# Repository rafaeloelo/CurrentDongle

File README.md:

# USB Power & Current Meter Dongle (v1.0)

A custom-designed, inline USB power, voltage, and current meter built from scratch—covering schematic capture, PCB layout in KiCad, hand-soldering assembly, and bare-metal C firmware development for the STM32G030 microcontroller.

---

## Key Features

* **High-Precision Sensing:** Uses the Texas Instruments **INA226** bi-directional current and power monitor with a 16-bit Delta-Sigma ADC over a **10 mOhm (0.01 Ohm)** shunt resistor.
* **Hardware Signal Filtering:** Configured for hardware-level averaging of **64 samples** (register value 0x4727), effectively smoothing out high-frequency switching noise and pulsed current draws typical of modern USB SMPS chargers.
* **Hardware Power Calculation:** Internal calibration register (CAL = 5120) enables direct hardware multiplication for current (0.1 mA/LSB) and power (2.5 mW/LSB) readings without burdening the Cortex-M0+ core, which lacks a hardware FPU.
* **Non-Blocking Firmware Architecture:** Fully asynchronous main loop driven by HAL_GetTick() state timers with zero HAL_Delay() calls during normal operation.
* **Low-Power Optimization:** Utilizes the Cortex-M0+ Sleep Mode via the __WFI() (Wait For Interrupt) instruction at the end of every loop cycle, keeping the CPU core asleep for ~95% of the time between SysTick interrupts.
* **Live Diagnostics:** Dual status LEDs indicating real-time I2C bus health for both the OLED display (0x3C) and the INA226 sensor (0x40) (solid = OK, rapid 10 Hz blinking = device disconnected/NACK).
* **Crisp UI:** 128x64 **SSD1306 OLED** display refreshed at 5 Hz (200 ms intervals) for optimal readability.

---

## Hardware Architecture & Specifications

| Parameter | Specification |
| :--- | :--- |
| **Microcontroller** | STM32G030 (ARM Cortex-M0+) |
| **Current/Voltage Sensor** | TI INA226 (I2C Address: 0x40) |
| **Shunt Resistor** | 10 mOhm (0.01 Ohm) |
| **Display** | SSD1306 OLED 128x64 (I2C Address: 0x3C) |
| **Passive Footprint Size** | **0805** (selected specifically for manual soldering) |
| **Toolchain** | STM32CubeMX, CMake, Ninja, arm-none-eabi-gcc |

---

## Hardware Bring-Up, Assembly & Design Notes (Rev 1.0)

This board was designed with manual assembly and ease of debugging in mind:

1. **Hand-Soldering Friendly (0805 Passives):**  
   All passive components (resistors, capacitors, inductors) were intentionally chosen in the **0805 package**, allowing the entire PCB to be assembled cleanly using a standard **pencil soldering iron** without requiring a reflow oven or hot-air station.
2. **Power Tree & Unpopulated LDO Stage (U3, R12, C9, C10 - DNP):**  
   The initial schematic included an LDO linear voltage regulator stage (U3 along with R12, C9, and C10) downstream of the step-down buck converter. During step-by-step hardware bring-up, testing of the assembled switching converter revealed a stable output of **3.35 V**. Because this is well within the safe operating specifications for the STM32G030, INA226, and SSD1306, the LDO stage was left unpopulated (**DNP**) and bypassed.
3. **External Crystal Oscillator (HSE vs. HSI):**  
   Although the external crystal oscillator and its load capacitors were soldered onto the board, the HSE clock source was left inactive in the firmware. The MCU runs reliably on its internal **HSI RC oscillator (16 MHz)**, which provides more than enough timing accuracy for I2C communication and UI refresh intervals.
4. **Mechanical Notes for Rev 2.0 (OLED Mounting Holes):**  
   The four corner mounting holes originally placed for mechanical standoffs under the OLED module proved unnecessary. Soldering the display via its standard THT pin header provides rigid, more than sufficient mechanical stability. These mounting holes will be removed in Revision 2.0 to reduce the overall PCB footprint.

---

## Gallery

### KiCad Design & 3D Render

### Assembled Hardware

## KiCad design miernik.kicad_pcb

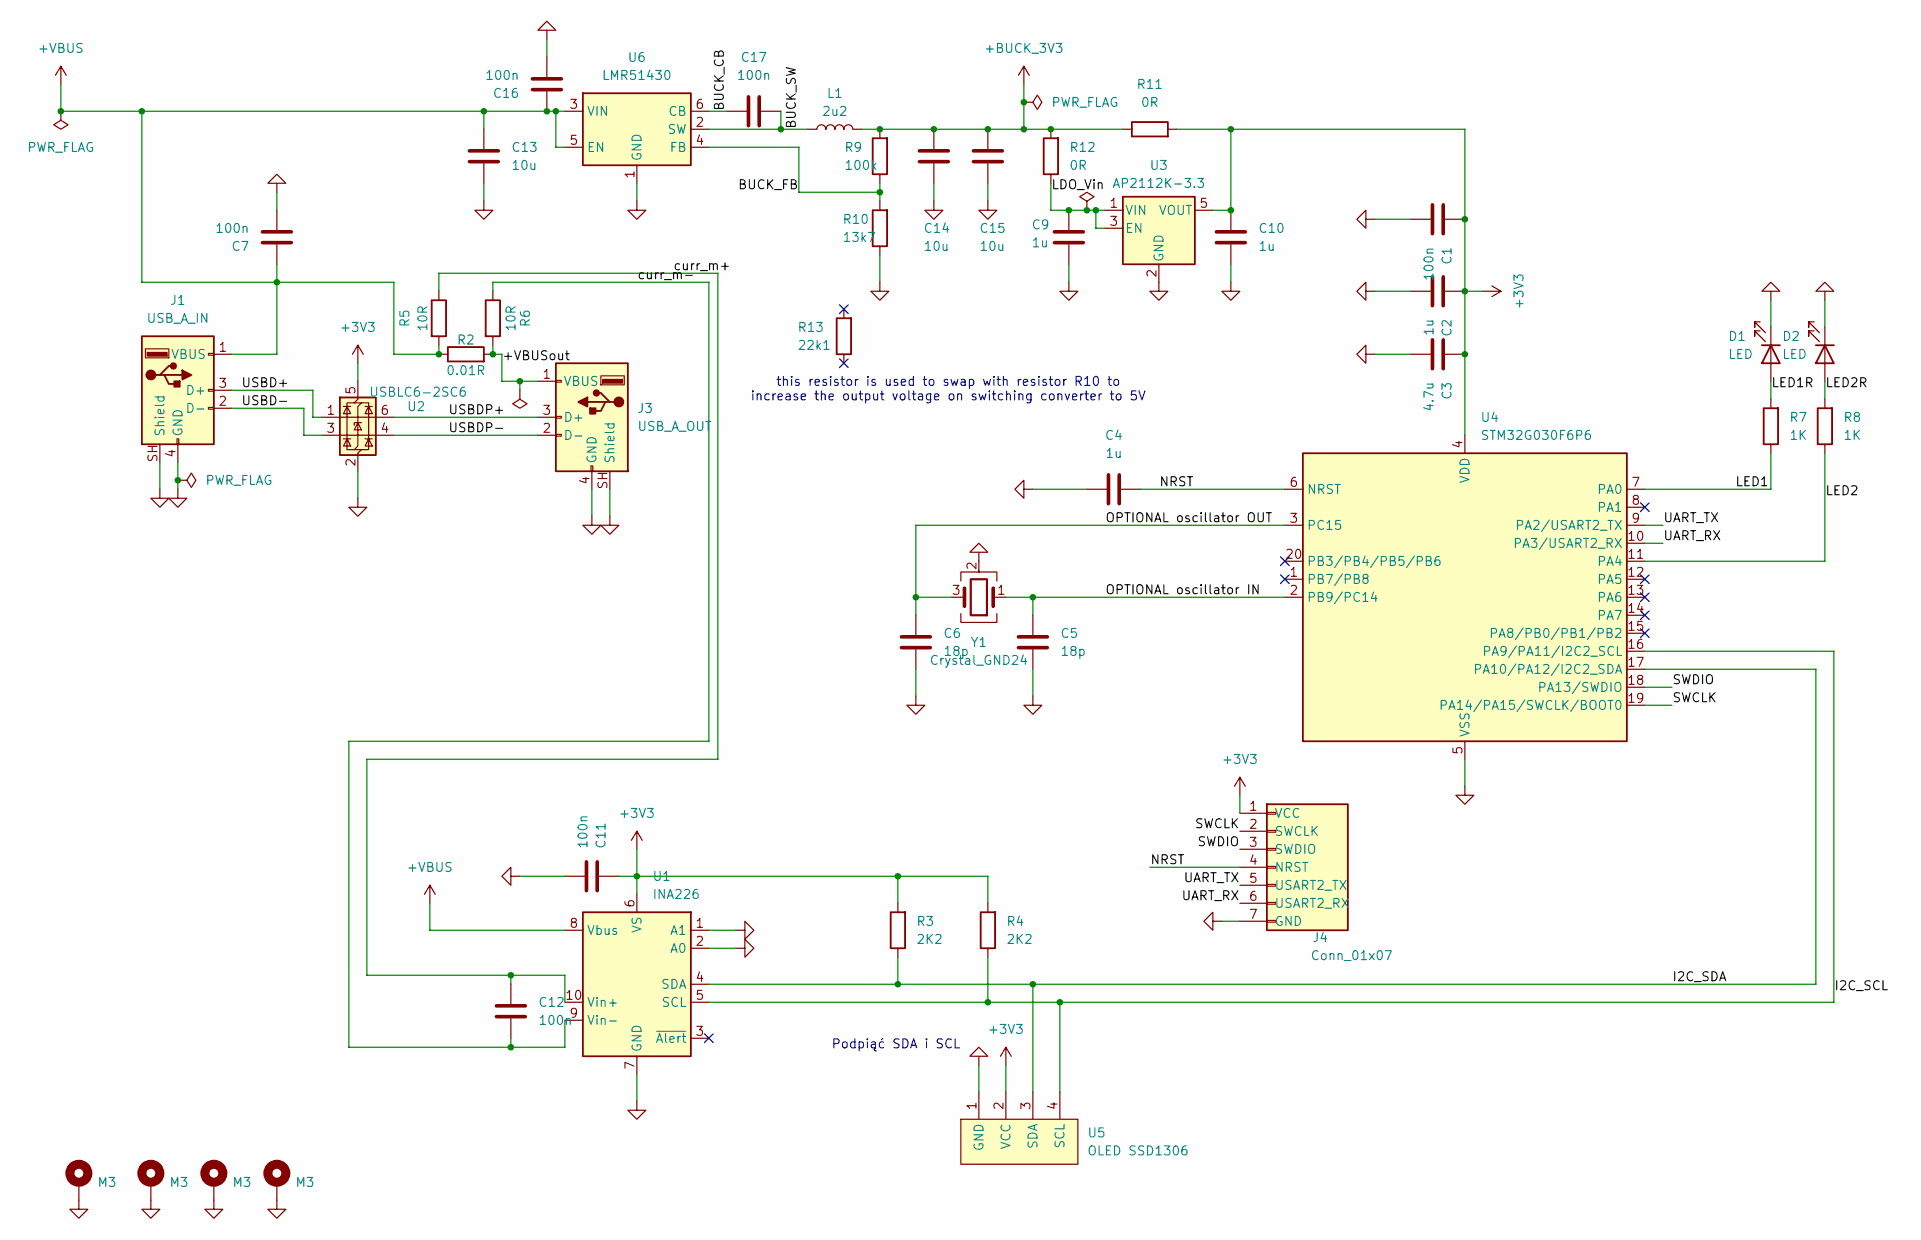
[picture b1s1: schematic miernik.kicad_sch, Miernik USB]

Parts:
C1, C7, C11, C12, C16, C17: 100n; C_0805_2012Metric
C2, C4, C9, C10: 1u; C_0805_2012Metric
C3: 4.7u; C_0805_2012Metric
C5, C6: 18p; C_0805_2012Metric
C13, C14, C15: 10u; C_0805_2012Metric
D1, D2: LED; LED_0805_2012Metric_Pad1.15x1.40mm_HandSolder
J1: USB_A_IN; USB_A_Molex_48037-2200_Horizontal
J3: USB_A_OUT; USB_A_Molex_67643_Horizontal
J4: Conn_01x07; PinSocket_1x07_P2.54mm_Vertical
L1: 2u2; L_0805_2012Metric_Pad1.05x1.20mm_HandSolder
MH1, MH2, MH3, MH4: M3; MountingHole_3.2mm_M3_Pad_Via
R2: 0.01R; R_2512_6332Metric_Pad1.40x3.35mm_HandSolder
R3, R4: 2K2; R_0805_2012Metric_Pad1.20x1.40mm_HandSolder
R5, R6: 10R; R_0805_2012Metric_Pad1.20x1.40mm_HandSolder
R7, R8: 1K; R_0805_2012Metric_Pad1.20x1.40mm_HandSolder
R9: 100k; R_0805_2012Metric_Pad1.20x1.40mm_HandSolder
R10: 13k7; R_0805_2012Metric_Pad1.20x1.40mm_HandSolder
R11, R12: 0R; R_0805_2012Metric_Pad1.20x1.40mm_HandSolder
R13: 22k1; R_0805_2012Metric_Pad1.20x1.40mm_HandSolder
U1: INA226; TSSOP-10_3x3mm_P0.5mm
U2: USBLC6-2SC6; SOT-23-6
U3: AP2112K-3.3; SOT-23-5
U4: STM32G030F6P6; TSSOP-20_4.4x6.5mm_P0.65mm
U5: OLED SSD1306; 128x64OLED
U6: LMR51430; SOT-23-6
Y1: Crystal_GND24; Crystal_SMD_3225-4Pin_3.2x2.5mm_HandSoldering

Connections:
+3V3: C1.1, C2.1, C3.1, C10.1, C11.1, J4.1 (VCC), R3.2, R4.2, R11.2, U1.6 (VS), U2.5 (VBUS), U3.5 (VOUT), U4.4 (VDD), U5.2 (VCC)
+BUCK_3V3: C14.1, C15.1, L1.2, R9.2, R11.1, R12.2
+VBUS: C7.1, C13.1, C16.1, J1.1 (VBUS), R2.1, R5.2, U1.8 (Vbus), U6.3 (VIN), U6.5 (EN)
/+VBUSout: J3.1 (VBUS), R2.2, R6.2
/BUCK_CB: C17.2, U6.6 (CB)
/BUCK_FB: R9.1, R10.2, U6.4 (FB)
/BUCK_SW: C17.1, L1.1, U6.2 (SW)
/I2C_SCL: R4.1, U1.5 (SCL), U4.16 (PA9/PA11/I2C2_SCL), U5.4 (SCL)
/I2C_SDA: R3.1, U1.4 (SDA), U4.17 (PA10/PA12/I2C2_SDA), U5.3 (SDA)
/LDO_Vin: C9.1, R12.1, U3.1 (VIN), U3.3 (EN)
/LED1: R7.1, U4.7 (PA0)
/LED1R: D1.2 (A), R7.2
/LED2: R8.1, U4.11 (PA4)
/LED2R: D2.2 (A), R8.2
/NRST: C4.1, J4.4 (NRST), U4.6 (NRST)
/OPTIONAL oscillator IN: C5.1, U4.2 (PB9/PC14), Y1.1
/OPTIONAL oscillator OUT: C6.1, U4.3 (PC15), Y1.3
/SWCLK: J4.2 (SWCLK), U4.19 (PA14/PA15/SWCLK/BOOT0)
/SWDIO: J4.3 (SWDIO), U4.18 (PA13/SWDIO)
/UART_RX: J4.6 (USART2_RX), U4.10 (PA3/USART2_RX)
/UART_TX: J4.5 (USART2_TX), U4.9 (PA2/USART2_TX)
/USBD+: J1.3 (D+), U2.1 (I/O1)
/USBD-: J1.2 (D-), U2.3 (I/O2)
/USBDP+: J3.3 (D+), U2.6 (I/O1)
/USBDP-: J3.2 (D-), U2.4 (I/O2)
/curr_m+: C12.1, R5.1, U1.10 (Vin+)
/curr_m-: C12.2, R6.1, U1.9 (Vin-)
GND: C1.2, C2.2, C3.2, C4.2, C5.2, C6.2, C7.2, C9.2, C10.2, C11.2, C13.2, C14.2, C15.2, C16.2, D1.1 (K), D2.1 (K), J1.4 (GND), J1.SH (Shield), J3.4 (GND), J3.SH (Shield), J4.7 (GND), MH1.1 (1_1), MH2.1 (1_1), MH3.1 (1_1), MH4.1 (1_1), R10.1, U1.1 (A1), U1.2 (A0), U1.7 (GND), U2.2 (GND), U3.2 (GND), U4.5 (VSS), U5.1 (GND), U6.1 (GND), Y1.2 (G), Y1.4 (G)

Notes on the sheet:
this resistor is used to swap with resistor R10 to increase the output voltage on switching converter to 5V
Podpiąć SDA i SCL

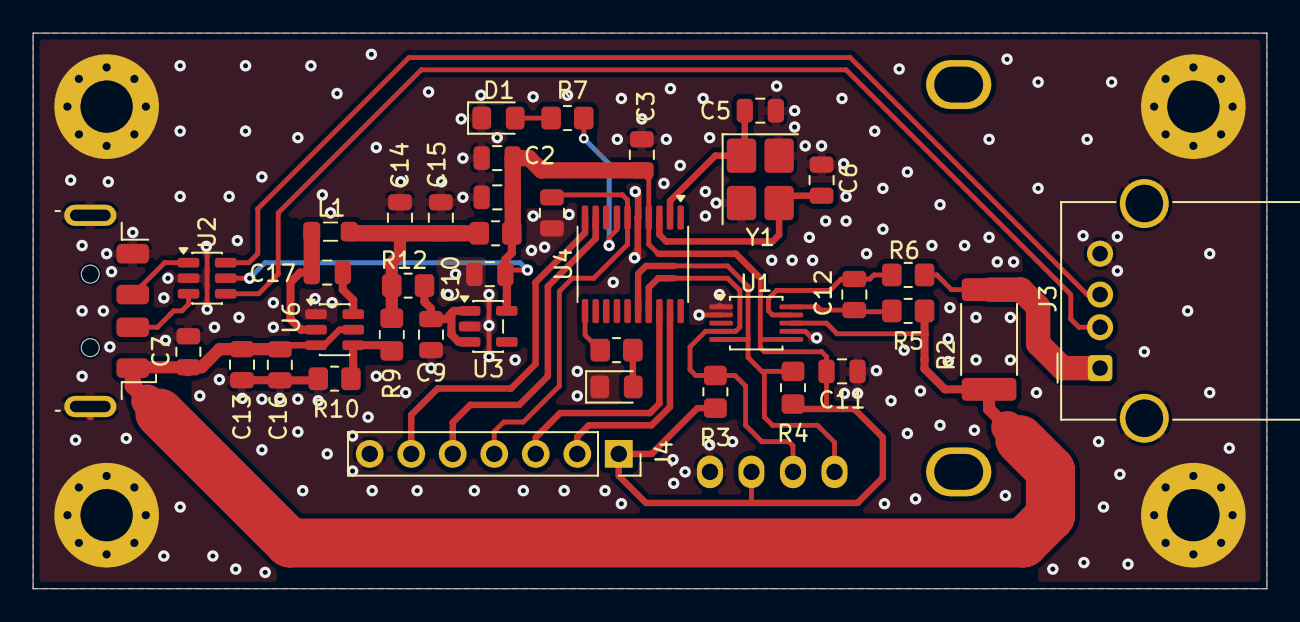
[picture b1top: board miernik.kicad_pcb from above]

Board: 2 copper layers, 75.5 x 34.0 mm, 44 parts (1 on the bottom side), 28 nets.

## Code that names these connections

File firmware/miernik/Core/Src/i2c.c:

/* USER CODE BEGIN Header */
/**
  ******************************************************************************
  * @file    i2c.c
  * @brief   This file provides code for the configuration
  *          of the I2C instances.
  ******************************************************************************
  * @attention
  *
  * Copyright (c) 2026 STMicroelectronics.
  * All rights reserved.
  *
  * This software is licensed under terms that can be found in the LICENSE file
  * in the root directory of this software component.
  * If no LICENSE file comes with this software, it is provided AS-IS.
  *
  ******************************************************************************
  */
/* USER CODE END Header */
/* Includes ------------------------------------------------------------------*/
#include "i2c.h"

/* USER CODE BEGIN 0 */

/* USER CODE END 0 */

I2C_HandleTypeDef hi2c2;

/* I2C2 init function */
void MX_I2C2_Init(void)
{

  /* USER CODE BEGIN I2C2_Init 0 */

  /* USER CODE END I2C2_Init 0 */

  /* USER CODE BEGIN I2C2_Init 1 */

  /* USER CODE END I2C2_Init 1 */
  hi2c2.Instance = I2C2;
  hi2c2.Init.Timing = 0x00503D58;
  hi2c2.Init.OwnAddress1 = 0;
  hi2c2.Init.AddressingMode = I2C_ADDRESSINGMODE_7BIT;
  hi2c2.Init.DualAddressMode = I2C_DUALADDRESS_DISABLE;
  hi2c2.Init.OwnAddress2 = 0;
  hi2c2.Init.OwnAddress2Masks = I2C_OA2_NOMASK;
  hi2c2.Init.GeneralCallMode = I2C_GENERALCALL_DISABLE;
  hi2c2.Init.NoStretchMode = I2C_NOSTRETCH_DISABLE;
  if (HAL_I2C_Init(&hi2c2) != HAL_OK)
  {
    Error_Handler();
  }

  /** Configure Analogue filter
  */
  if (HAL_I2CEx_ConfigAnalogFilter(&hi2c2, I2C_ANALOGFILTER_ENABLE) != HAL_OK)
  {
    Error_Handler();
  }

  /** Configure Digital filter
  */
  if (HAL_I2CEx_ConfigDigitalFilter(&hi2c2, 0) != HAL_OK)
  {
    Error_Handler();
  }
  /* USER CODE BEGIN I2C2_Init 2 */

  /* USER CODE END I2C2_Init 2 */

}

void HAL_I2C_MspInit(I2C_HandleTypeDef* i2cHandle)
{

  GPIO_InitTypeDef GPIO_InitStruct = {0};
  if(i2cHandle->Instance==I2C2)
  {
  /* USER CODE BEGIN I2C2_MspInit 0 */

  /* USER CODE END I2C2_MspInit 0 */

    __HAL_RCC_GPIOA_CLK_ENABLE();
    /**I2C2 GPIO Configuration
    PA11 [PA9]     ------> I2C2_SCL
    PA12 [PA10]     ------> I2C2_SDA
    */
    GPIO_InitStruct.Pin = GPIO_PIN_11|GPIO_PIN_12;
    GPIO_InitStruct.Mode = GPIO_MODE_AF_OD;
    GPIO_InitStruct.Pull = GPIO_NOPULL;
    GPIO_InitStruct.Speed = GPIO_SPEED_FREQ_LOW;
    GPIO_InitStruct.Alternate = GPIO_AF6_I2C2;
    HAL_GPIO_Init(GPIOA, &GPIO_InitStruct);

    /* I2C2 clock enable */
    __HAL_RCC_I2C2_CLK_ENABLE();
  /* USER CODE BEGIN I2C2_MspInit 1 */

  /* USER CODE END I2C2_MspInit 1 */
  }
}

void HAL_I2C_MspDeInit(I2C_HandleTypeDef* i2cHandle)
{

  if(i2cHandle->Instance==I2C2)
  {
  /* USER CODE BEGIN I2C2_MspDeInit 0 */

  /* USER CODE END I2C2_MspDeInit 0 */
    /* Peripheral clock disable */
    __HAL_RCC_I2C2_CLK_DISABLE();

    /**I2C2 GPIO Configuration
    PA11 [PA9]     ------> I2C2_SCL
    PA12 [PA10]     ------> I2C2_SDA
    */
    HAL_GPIO_DeInit(GPIOA, GPIO_PIN_11);

    HAL_GPIO_DeInit(GPIOA, GPIO_PIN_12);

  /* USER CODE BEGIN I2C2_MspDeInit 1 */

  /* USER CODE END I2C2_MspDeInit 1 */
  }
}

/* USER CODE BEGIN 1 */

/* USER CODE END 1 */
